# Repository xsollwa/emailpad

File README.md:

# Emailpad
*This is a macropad designed to speed up email writing process. It has 3 buttons for commonly used email phrases and a rotary encoder to quickly switch between fields!*

## Features 

- **3 Macro Buttons:**

 Button 1 - Common email intro ("I hope this email finds you well.")
 
 Button 2 - Common closing ("Best wishes,\nRuzanna")
 
 Button 3 - Follow up reminder ("Please let me know if you have any questions")

- **Rotary encoder**

 1 Clockwise - Scroll up between email app fields (Tab)
 
 2 Counterclockwise - Scroll down between email app fields (Shift+Tab)
  
- Custom pcb (using KiCAD)
- Custom 3d model (using OnShape)
- KMK firmware (using Python)
- SK6812 MINI-E LEDs

## Images 

**CAD**

*Case components & fit*

**PCB**

## Bill of Materials 
| Quantity | Material               | Description                        |
|----------|------------------------|------------------------------------|
| 1        | Seeed XIAO RP2040      | USB-C Microcontroller              |
| 3        | MX-Style switches      | Macro keys                         |
| 1        | EC11 Rotary encoder    | Tab navigation                     |
| 2        | 1N4148 Diodes          | For encoder & Microcontroller      |
| 2        | SK6812MINI-E LEDs      | Lighting                           |
| 1        | Custom PCB             | Custom printable circuit board     |
| 1        | 3d printed Case        | Enclosure for parts                |
| 4        | M3x16mm screws         | For assembly                       |

## Firmware
The firmware is writen in Python using KMK Firmware.

**Pins**

Button 1 - GP27

Button 2 - GP28

Button 3 - GP29

Encoder A - GP0

Encoder B - GP1

### Instructions

1 - Install KMK into your XIAO RP2040,

2 - Upload the firmware on the device's USB flash drive as .py,

3 - You can also customize it by substituting the email phrases with the ones you use!

*Created by Ruzanna Gaboyan!*

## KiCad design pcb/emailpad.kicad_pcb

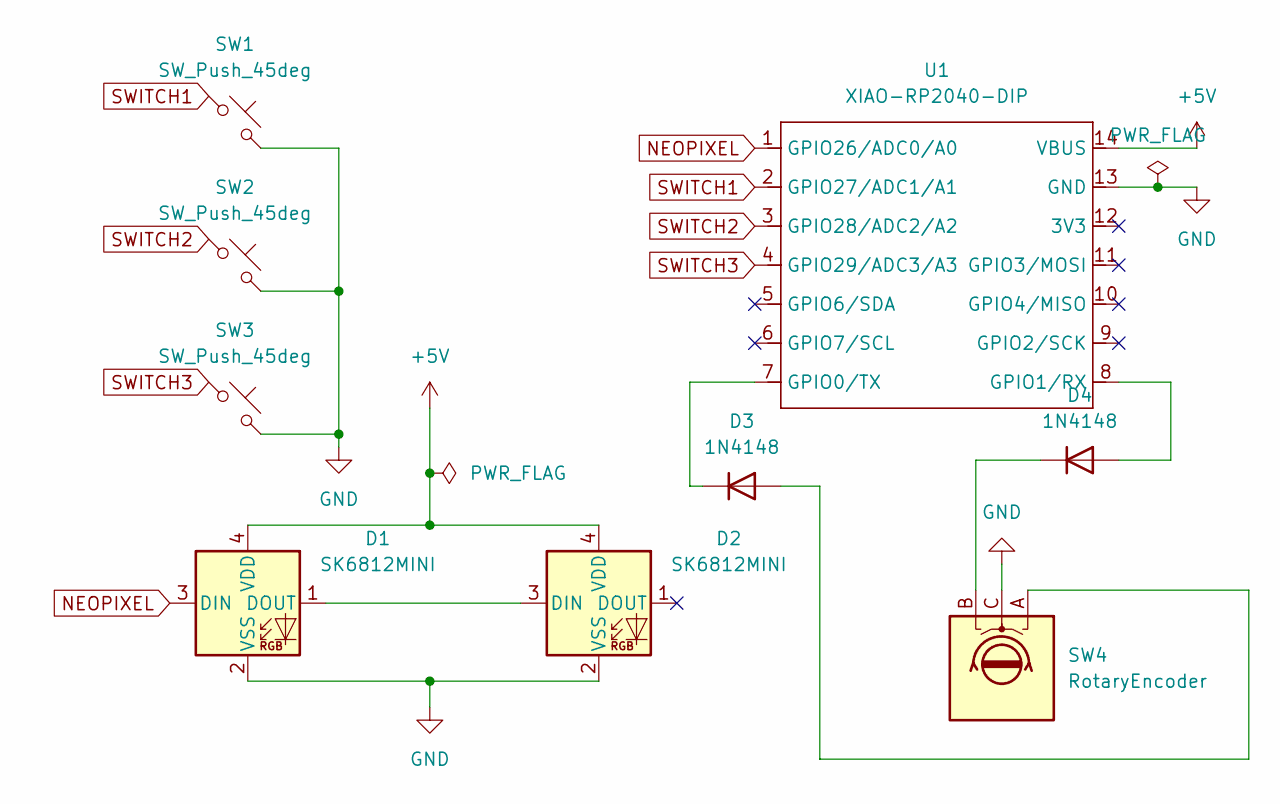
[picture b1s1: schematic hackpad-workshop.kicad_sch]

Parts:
D1, D2: SK6812MINI; LED_SK6812MINI_PLCC4_3.5x3.5mm_P1.75mm
D3, D4: 1N4148; D_DO-35_SOD27_P7.62mm_Horizontal
SW1, SW2, SW3: SW_Push_45deg; SW_Cherry_MX_1.00u_PCB
SW4: RotaryEncoder; RotaryEncoder_Alps_EC11E-Switch_Vertical_H20mm
U1: XIAO-RP2040-DIP

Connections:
+5V: D1.4 (VDD), D2.4 (VDD), U1.14 (VBUS)
GND: D1.2 (VSS), D2.2 (VSS), SW1.2, SW2.2, SW3.2, SW4.C, U1.13 (GND)
NEOPIXEL: D1.3 (DIN), U1.1 (GPIO26/ADC0/A0)
unnamed: D1.1 (DOUT), D2.3 (DIN)
unnamed: D3.2 (A), SW4.A
unnamed: D3.1 (K), U1.7 (GPIO0/TX)
unnamed: D4.2 (A), U1.8 (GPIO1/RX)
unnamed: D4.1 (K), SW4.B
SWITCH1: SW1.1, U1.2 (GPIO27/ADC1/A1)
SWITCH2: SW2.1, U1.3 (GPIO28/ADC2/A2)
SWITCH3: SW3.1, U1.4 (GPIO29/ADC3/A3)

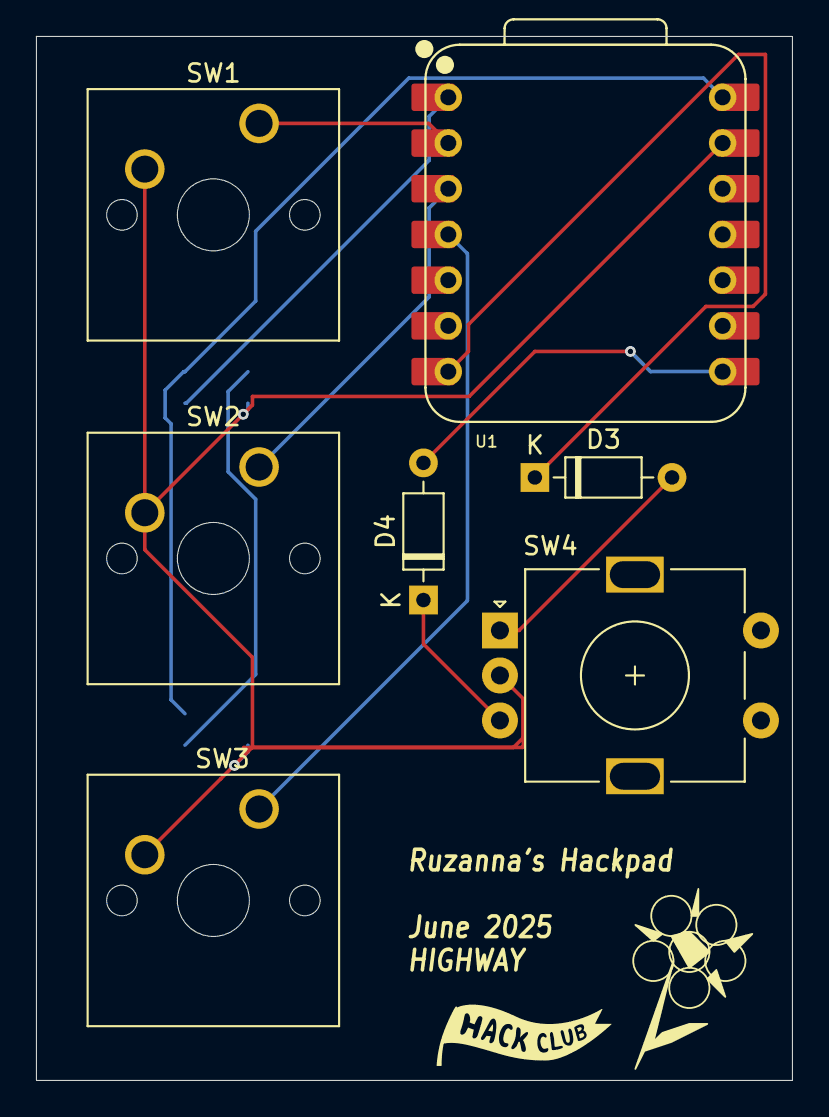
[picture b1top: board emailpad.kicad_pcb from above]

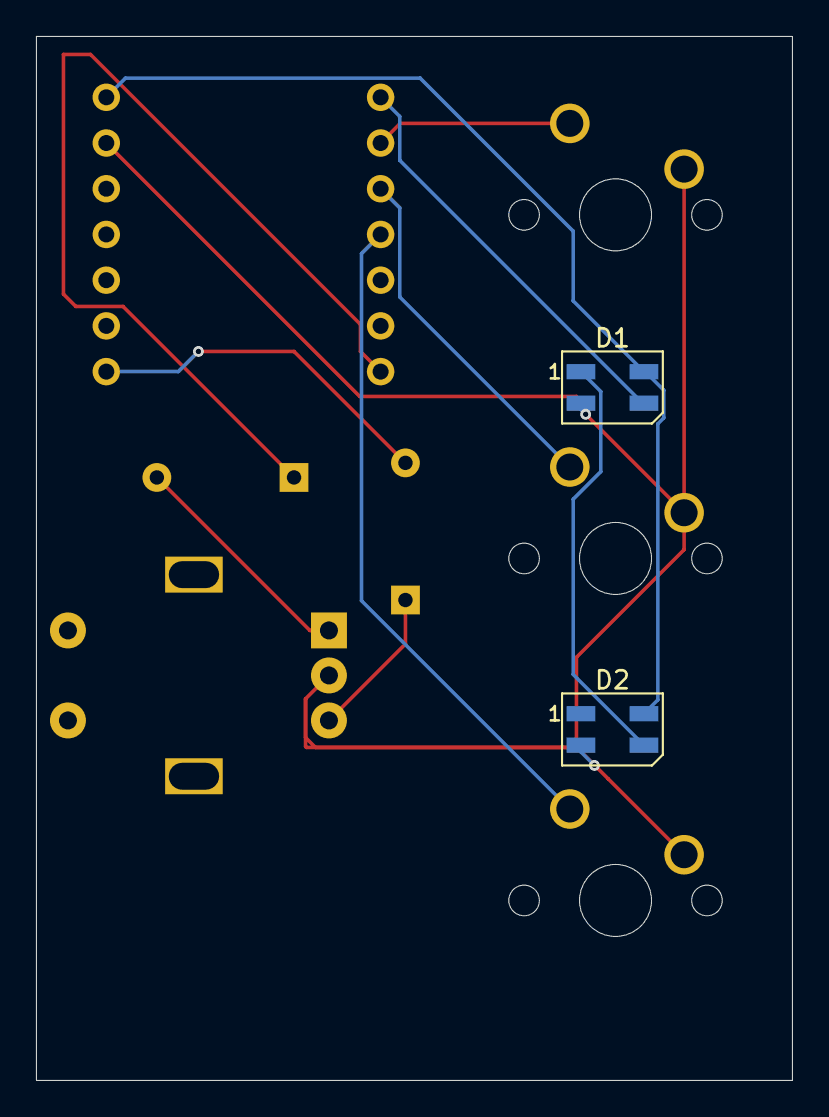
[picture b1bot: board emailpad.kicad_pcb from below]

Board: 2 copper layers, 42.0 x 58.0 mm, 9 parts (2 on the bottom side), 11 nets.

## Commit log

2025-06-18 Create file
2025-06-18 Rename Screenshot 2025-06-17 235204.png to top-view.png
2025-06-18 Rename Screenshot 2025-06-17 235322.png to side-view.png
2025-06-18 Rename Screenshot 2025-06-17 235538.png to top-view.png
2025-06-18 Rename Screenshot 2025-06-17 235538.png to front-view.png
2025-06-19 Rename hackpad-workshop.kicad_prl to emailpad.kicad_prl
2025-06-19 Rename hackpad-workshop.kicad_pro to emailpad.kicad_pro
